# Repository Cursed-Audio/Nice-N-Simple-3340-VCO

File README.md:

# Nice-N-Simple-3340-VCO
version 3 of my basic beginner friendly eurorack module.

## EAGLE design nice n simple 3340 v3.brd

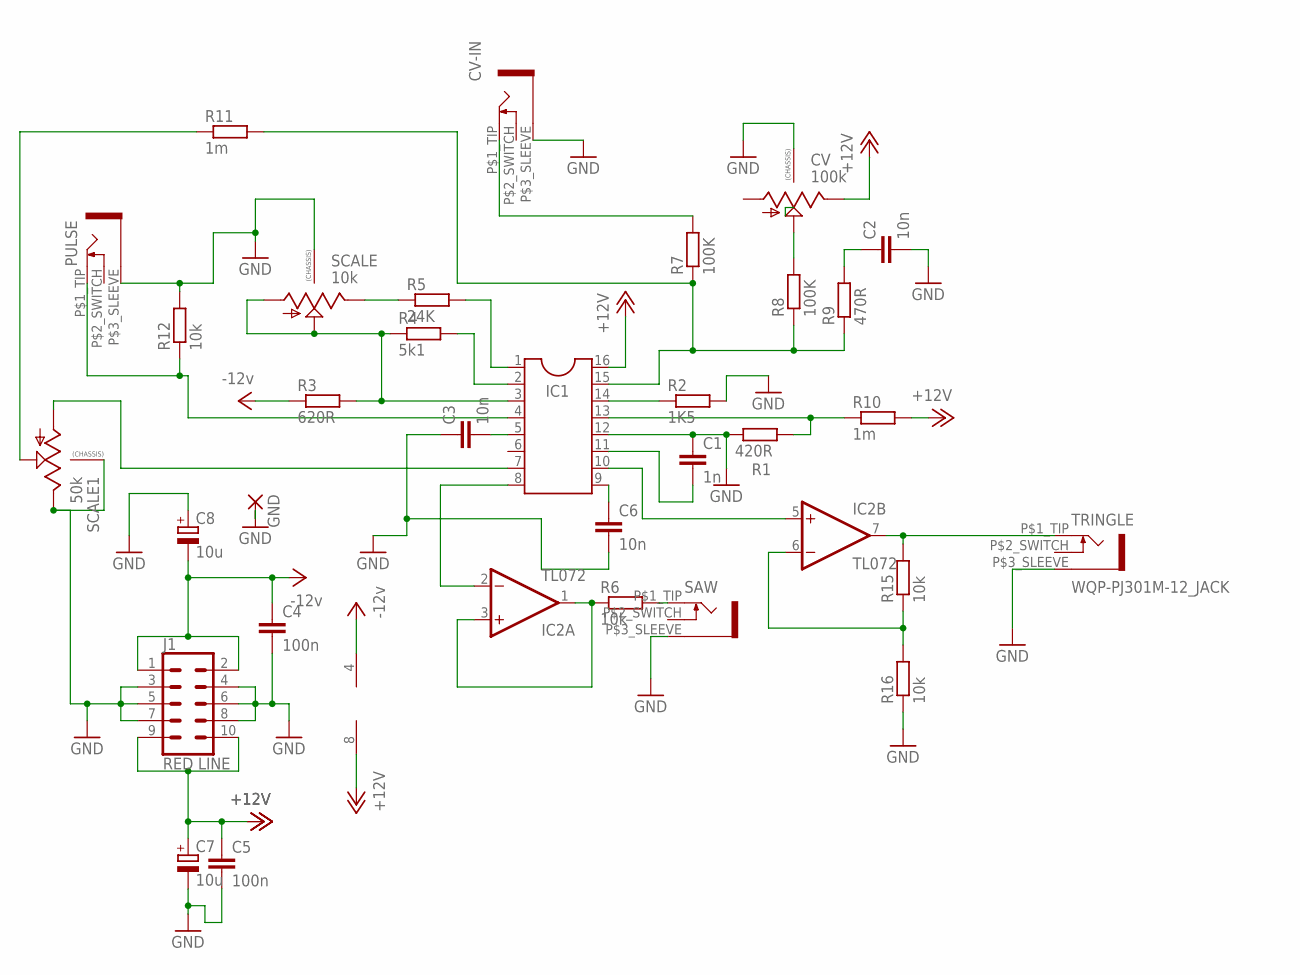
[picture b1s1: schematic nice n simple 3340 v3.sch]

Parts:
C1: 1n; C5B2.5
C2, C3, C6: 10n; C5B2.5
C4, C5: 100n; C5B2.5
C7, C8: 10u; E1,8-4
CV: 100k; 9MM_SNAP-IN_POT
CV-IN: WQP-PJ301M-12_JACK
GND: WIREPAD1,6/0,9; 1,6/0,9
IC1: CEM3340; SOCKET-16
IC2: TL072; DIL08
J1: RED LINE; 2X5-SHROUDED-NS
PULSE: WQP-PJ301M-12_JACK
R1: 420R; 0207/7
R2: 1K5; 0207/7
R3: 620R; 0207/7
R4: 5k1; 0207/7
R5: 24K; 0207/7
R6, R12, R15, R16: 10k; 0207/7
R7, R8: 100K; 0207/7
R9: 470R; 0207/7
R10, R11: 1m; 0207/7
SAW: WQP-PJ301M-12_JACK
SCALE: 10k; 9MM_SNAP-IN_POT
SCALE1: 50k; 9MM_SNAP-IN_POT
TRINGLE: WQP-PJ301M-12_JACK

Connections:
+12V: C5.1, C7.+, CV.3 (E), IC1.16, IC2.8 (V+), J1.9, J1.10, R10.2
-12V: C4.1, C8.-, IC2.4 (V-), J1.1, J1.2, R3.1
GND: C1.1, C2.2, C3.1, C4.2, C5.2, C6.2, C7.-, C8.+, CV.CHASSIS1, CV.CHASSIS2, CV-IN.P$3_SLEEVE (1), GND.1, IC1.12, J1.3, J1.4, J1.5, J1.6, J1.7, J1.8, PULSE.P$3_SLEEVE (1), R1.1, R2.2, R12.2, R16.1, SAW.P$3_SLEEVE (1), SCALE.CHASSIS1, SCALE.CHASSIS2, SCALE1.3 (E), SCALE1.CHASSIS1, SCALE1.CHASSIS2, TRINGLE.P$3_SLEEVE (1)
unnamed: R5.1, SCALE.3 (E)
unnamed: IC1.3, R3.2, R4.1, SCALE.1 (A), SCALE.2 (S)
unnamed: C1.2, IC1.11
unnamed: IC1.15, R7.1, R8.1, R9.1, R11.2
unnamed: IC1.13, R1.2, R10.1
unnamed: IC1.14, R2.1
unnamed: IC1.4, PULSE.P$1_TIP (2), R12.1
unnamed: IC1.2, R4.2
unnamed: C6.1, IC1.9
unnamed: C3.2, IC1.5
unnamed: IC1.1, R5.2
unnamed: IC2.6 (-IN), R15.1, R16.2
unnamed: IC1.8, IC2.2 (-IN)
unnamed: CV-IN.P$1_TIP (2), R7.2
unnamed: IC1.10, IC2.5 (+IN)
unnamed: IC2.1 (OUT), IC2.3 (+IN), R6.1
unnamed: R6.2, SAW.P$1_TIP (2)
unnamed: IC2.7 (OUT), R15.2, TRINGLE.P$1_TIP (2)
unnamed: IC1.7, SCALE1.1 (A)
unnamed: R11.1, SCALE1.2 (S)
unnamed: C2.1, R9.2
unnamed: CV.2 (S), R8.2

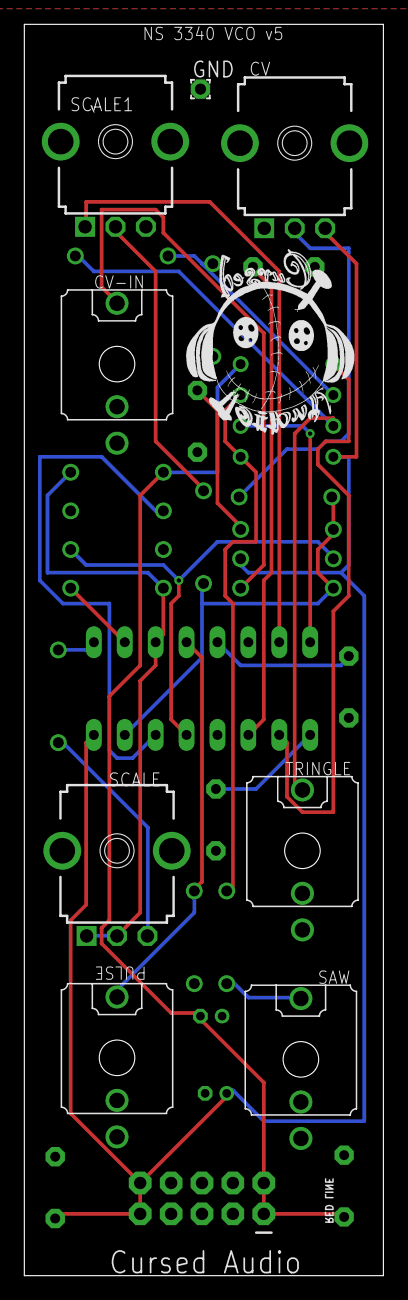
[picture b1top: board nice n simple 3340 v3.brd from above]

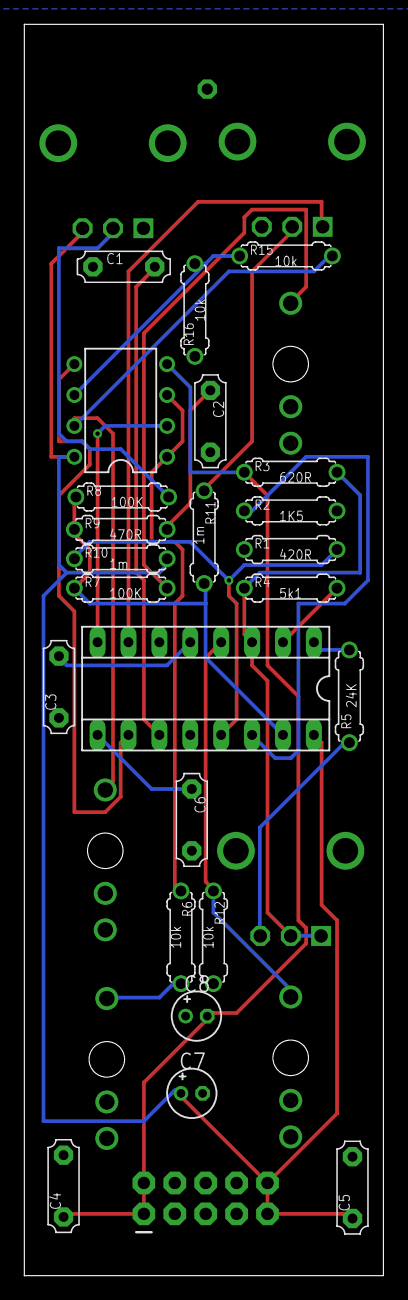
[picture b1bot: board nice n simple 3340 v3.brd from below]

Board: 2 copper layers, 29.5 x 102.9 mm, 34 parts (26 on the bottom side), 25 nets.

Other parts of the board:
U$1: CA

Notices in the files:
parts and their libraries:
SparkFun-Connectors: Licensing: Creative Commons ShareAlike 4.0 International - https://creativecommons.org/licenses/by-sa/4.0
